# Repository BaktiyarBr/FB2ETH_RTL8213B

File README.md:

# FB2ETH for OpenIPC

A small fiber-to-Ethernet media converter board for [OpenIPC](https://openipc.org) cameras. It connects a camera's 10/100 Ethernet port to a single-fiber BiDi SFP optical module, so the camera can be linked over optical fiber instead of copper.

The board is designed in KiCad 10.

## How it works

| Block | Part | Role |
|-------|------|------|
| Ethernet / SerDes switch | **RTL8213B-CG** (U1) | Bridges the camera's copper Ethernet (MDI) to the SFP's high-speed serial lanes |
| Power | **MP9943GQ-Z** (U3) + 10 µH inductor (L2) | Buck converter that makes the +3V3 rail from the camera's VBUS |
| Clock | 25 MHz crystal (X2) | Reference clock for the RTL8213B |
| Status | 3 × 0402 LEDs (PWR1, P6S1, P6S2) | Power and port link/activity |
| Camera side | **J1** – JST SH 1.0 mm, 6-pin | Ethernet + power from the camera |
| Fiber side | **J2** – 9-pin SFP BiDi module socket | Optical transceiver |

### J1 – camera connector (JST SH, 6-pin)

| Pin | Signal |
|-----|--------|
| 1 | ETH_TX+ |
| 2 | ETH_TX− |
| 3 | ETH_RX+ |
| 4 | ETH_RX− |
| 5 | GND |
| 6 | VBUS (power in) |

### J2 – SFP BiDi module (9-pin)

| Pin | Signal |
|-----|--------|
| 1 | GND |
| 2 | RXP |
| 3 | RXN |
| 4 | SD (signal detect) |
| 5, 6 | +3V3 |
| 7 | SFP_TX_N |
| 8 | SFP_TX_P |
| 9 | GND |

## Repository layout

```
FB2ETH_3/FB2ETH_3/     Current revision (4-layer PCB) — start here
  FB2ETH_3.kicad_pro   KiCad project
  FB2ETH_3.kicad_sch   Schematic
  FB2ETH_3.kicad_pcb   PCB layout
  FB2ETH_3.kicad_dru   Custom design rules
  FB2ETH_3.csv         Full BOM with LCSC part numbers
  production/          Gerbers (zip), BOM, pick-and-place, IPC netlist for JLCPCB
FB2ETH_2/FB2ETH_2/     Previous revision
FB2ETH/                First revision
from_epro/             Original EasyEDA Pro design imported into KiCad (reference)
projectLibs.pretty/    Project footprints (SFP connectors, QFN-8 for MP9943)
```

The `*-backups/` folders are KiCad's automatic project backups.

## Manufacturing

The `production/` folder of each revision is generated with the KiCad [Fabrication Toolkit](https://github.com/bennymeg/Fabrication-Toolkit) plugin (settings in `fabrication-toolkit-options.json`) and is ready to upload to JLCPCB:

- `FB2ETH_3.zip` – Gerber and drill files
- `bom.csv` – bill of materials for assembly
- `positions.csv` – component placement (CPL)

To regenerate them, open `FB2ETH_3.kicad_pcb` in KiCad and run **Fabrication Toolkit** from the PCB editor's plugin menu.

## Opening the project

1. Install [KiCad](https://www.kicad.org/) 10 or newer.
2. Open `FB2ETH_3/FB2ETH_3/FB2ETH_3.kicad_pro`.
3. If footprints show as missing, add `projectLibs.pretty` to the project's footprint library table under the nickname `projectLibs`.

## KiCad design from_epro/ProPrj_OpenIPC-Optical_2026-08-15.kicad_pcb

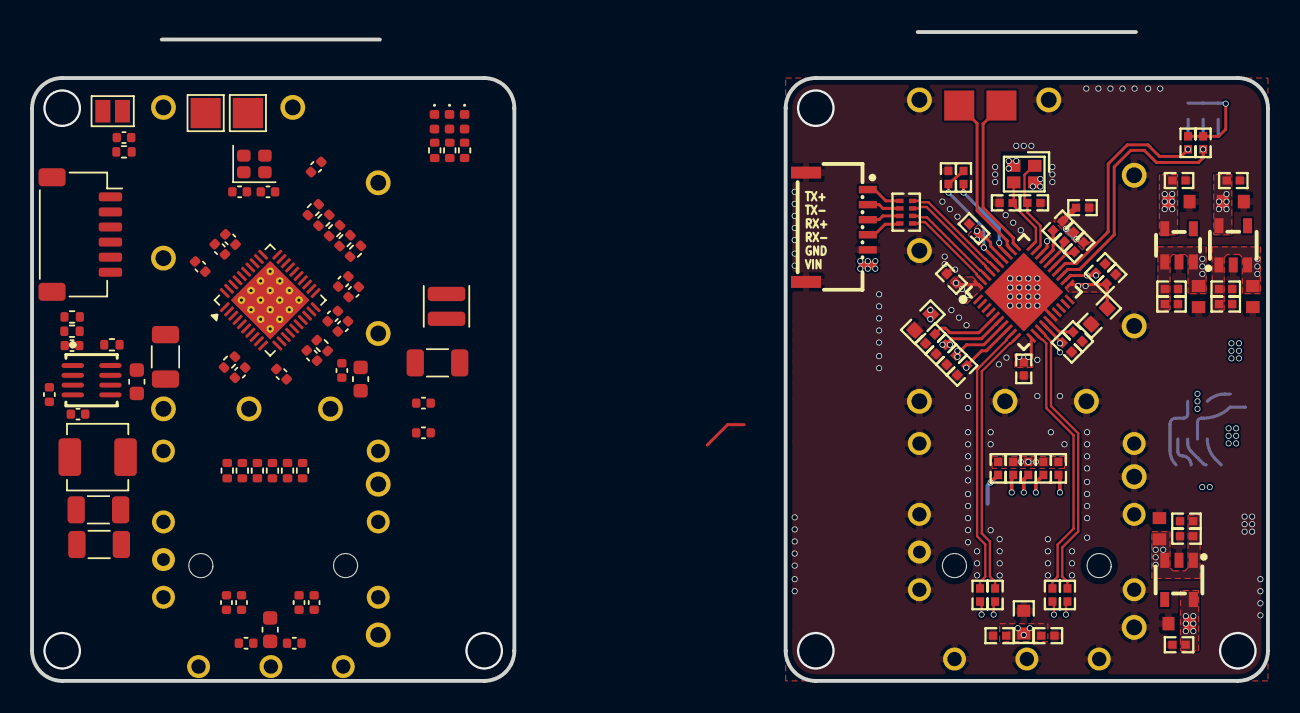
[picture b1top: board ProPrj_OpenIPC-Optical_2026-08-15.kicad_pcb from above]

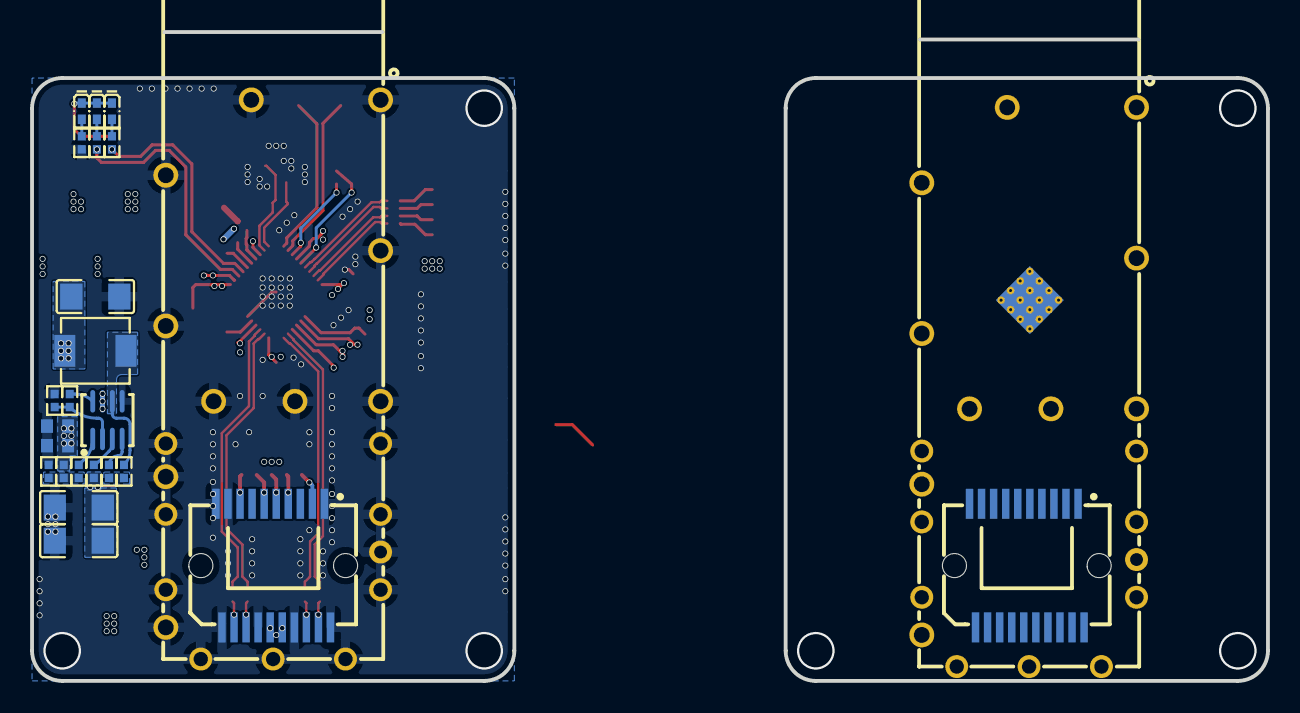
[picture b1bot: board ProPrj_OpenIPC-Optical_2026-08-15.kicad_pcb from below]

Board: 4 copper layers, 82.0 x 43.0 mm, 149 parts (25 on the bottom side), 92 nets.

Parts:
C1, C2#2: 18pF; C_0402_1005Metric
C1#2, C2, C3, C4, C5, C6, C7, C8, C10, C11, C12, C13, C14, C46, C68, C70, C71, C72, C73, C76, C81, C85, C88, C96, C97, C99, C100, C102: R0402
C9, C69, C75: R0603
C15, C16, C17, C18, C21, C22, C23, C26, C27, C28, C29, C30, C31, C32, C33, C35, C36, C38, C39, C40, C41, C42, C43, C44: 100n; C_0402_1005Metric
C15#2, C77, C80, C84, C94, C95, C98, C101: C0603
C18#2, C19#2, C93: C1206
C19, C20: 22u; C_1206_3216Metric
C20#2, C78: C0402
C24: 100n; C_0603_1608Metric
C25, C34: 10u; C_1206_3216Metric
C37, C45: 1u; C_0603_1608Metric
CN1: HC-SFP-20P; CONN-SMD_20P-P0.80_HCTL_HC-SFP-20P
CN1#2: CONN-SMD_20P-P0.80_HCTL_HC-SFP-20P
J1: Conn_01x06_MountingPin; JST_SH_SM06B-SRSS-TB_1x06-1MP_P1.00mm_Horizontal
JP1: SolderJumper_2_Open; SolderJumper-2_P1.3mm_Open_Pad1.0x1.5mm
L1: 2u2; L_Changjiang_FTC252012S
L1#2: IND-SMD_L4.4-W4.2
L2: 10uH; L_Changjiang_FXL0420
P6S0, P6S1#2: LED0402-RD
P6S1, P6S2: LED_0402_1005Metric
PWR: LED0402-RD
PWR1: LED_0402_1005Metric
R1, R2, R3, R4, R10, R11#2, R95#2: 4.7kΩ; R_0402_1005Metric
R1#2, R2#2, R3#2, R4#2, R5#2, R6#2, R9#2, R10#2, R11, R16, R17, R20, R82, R83, R86, R87#2, R90, R95, R96, R97, R98, R99#2: R0402
R5, R6, R99: 470Ω; R_0402_1005Metric
R7, R12: 100k; R_0402_1005Metric
R8: 43k; R_0402_1005Metric
R9: 2.49kΩ; R_0402_1005Metric
R13: 1k; R_0402_1005Metric
R82#2, R83#2, R86#2, R87, R90#2: 10kΩ; R_0402_1005Metric
RN1: RES-ARRAY-SMD_0402-8P-L2.0-W1.0-BL
SCK: Test-Point-0.5mm
SCK1: TestPoint_Pad_2.0x2.0mm
SDA: Test-Point-0.5mm
SDA1: TestPoint_Pad_2.0x2.0mm
TOMinBoard: CONN-SMD_6P-P1.00_HDGC1002WR-S-6P
U1: RTL8213B-CG; VQFN-40-1EP_5x5mm_P0.4mm_EP3.7x3.7mm_ThermalVias
U1#2: QFN-40_L5.0-W5.0-P0.40-BL-EP3.7
U2: QFN-8_L3.0-W3.0-P0.65-BL
U3: MP9943GQ-Z; QFN-8_L3.0-W3.0-P0.65-BL
U6: TH_HC-SFP-01L
U6#2: TH_HC-SFP-01L
U7, U8: SOT-23-5_L3.0-W1.7-P0.95-LS2.8-BR
U10: SOT-23-5_L2.9-W1.6-P0.95-LS2.8-BL
X2: 25MHz; Crystal_SMD_2016-4Pin_2.0x1.6mm
X2#2: CRYSTAL-SMD_4P-L2.0-W1.6-BL

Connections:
4V5: C15#2.2, C46.1, C77.2, C81.2, C85.2, C88.1, C93.1, C94.2, C95.2, C99.2, C100.1, C101.2, L1#2.2, R17.2, U7.1, U7.3, U8.1, U8.3, U10.1, U10.3
8213B_1V0: C3.2, C4.2, C5.2, C6.2, C7.2, C8.2, C75.2, C98.2, C102.1, U1#2.6, U1#2.8, U1#2.11, U1#2.22, U1#2.34, U1#2.40, U10.5
8213B_3V3: C9.2, C10.2, C11.2, C12.2, C13.2, C14.2, C80.2, C96.1, P6S0.1, P6S1#2.1, PWR.1, R1#2.2, R2#2.1, R3#2.2, R4#2.2, R10#2.2, R95.2, U1#2.7, U1#2.14, U1#2.21, U1#2.28, U1#2.35, U7.5
8213B_EN_SWR: R11.2, U1#2.15
8213B_SCK: SCK.1, U1#2.32
8213B_SDA: SDA.1, U1#2.31
$1N1852: C1#2.1, U1#2.29, X2#2.1
$1N1863: R10#2.1, U1#2.33
$1N1904: R9#2.2, U1#2.5
$1N1912: C2.2, U1#2.30, X2#2.3
$1N1945: P6S1#2.2, R5#2.2
$1N1946: P6S0.2, R6#2.2
$1N2817: CN1#2.5, R86.1
$1N2818: CN1#2.4, R83.1
$1N2820: CN1#2.6, R87#2.1
$1N2821: CN1#2.2, R82.1
$1N2827: CN1#2.8, R90.1
$1N6453: PWR.2, R99#2.2
$2N900: R97.2, U2.8
$2N902: C20#2.2, R98.2
$2N903: C78.2, R97.1, U2.2
$2N910: R16.2, R17.1, R20.2
$2N915: C20#2.1, U2.4
$2N918: R96.2, U2.3
+1V1: C28.1, C29.1, C30.1, C31.1, C32.1, C33.1, C34.1, L1.1, U1.6 (AVDDL), U1.8 (DVDDL), U1.11 (SVDDL), U1.22 (DVDDL), U1.34 (PLLVDDL), U1.40 (AVDDL)
+3V3: C16.1, C18.1, C19.1, C20.1, C21.1, C22.1, C26.1, C27.1, C35.1, C36.1, C37.1, C42.1, C43.1, C44.1, C45.1, CN1.15, CN1.16, L2.2, P6S1.1 (A), P6S2.1 (A), PWR1.1 (A), R1.2, R2.1, R3.2, R4.2, R7.1, R10.2, R11#2.1, R82#2.2, R83#2.2, R86#2.2, R87.2, R90#2.2, R95#2.2, U1.7 (AVDDH), U1.14 (AVDDH), U1.19 (HV_SWR), U1.20 (HV_SWR), U1.21 (DVDDIO), U1.28 (AVDDH), U1.35 (AVDDH)
/8213B_SCK: SCK1.1 (1_1), U1.32 (SCK)
/8213B_SDA: SDA1.1 (1_1), U1.31 (SDA)
/ETH_RX+: J1.3, U1.38 (P3MDIBP)
/ETH_RX-: J1.4, U1.39 (P3MDIBN)
/ETH_TX+: J1.1, U1.36 (P3MDIAP)
/ETH_TX-: J1.2, U1.37 (P3MDIAN)
/HSIN: C41.2, U1.13 (HSIN)
/HSIP: C40.2, U1.12 (HSIP)
/HSON: C38.2, U1.9 (HSON)
/HSOP: C39.2, U1.10 (HSOP)
/P3LED0: R1.1, U1.27 (GPO52/P3LED0/SMI_SEL)
/P3LED1: R95#2.1, U1.26 (GPIO51/P3LED1)
/P3LED2: R2.2, U1.25 (GPO50/P3LED2/EN_PHY)
/P6LED0: R3.1, R6.1, U1.24 (GPIO48/P6LED0/MID29)
/P6LED1: R4.1, R5.1, U1.23 (GPO45/P6LED1/DISAUTOLOAD)
/SFP_RX_N: C41.1, CN1.12
/SFP_RX_P: C40.1, CN1.13
/SFP_TX_N: C38.1, CN1.19
/SFP_TX_P: C39.1, CN1.18
ETH_RX+: RN1.2, TOMinBoard.3
ETH_RX-: RN1.1, TOMinBoard.4
ETH_TX+: RN1.4, TOMinBoard.1
ETH_TX-: RN1.3, TOMinBoard.2
FB_5V: R16.1, U2.1
GND: C1.2, C1#2.2, C2.1, C2#2.1, C3.1, C4.1, C5.1, C6.1, C7.1, C8.1, C9.1, C10.1, C11.1, C12.1, C13.1, C14.1, C15.2, C15#2.1, C16.2, C18#2.1, C19.2, C19#2.1, C20.2, C21.2, C22.2, C23.2, C24.2, C25.2, C26.2, C27.2, C28.2, C29.2, C30.2, C31.2, C32.2, C33.2, C34.2, C35.2, C36.2, C37.2, C42.2, C43.2, C44.2, C45.2, C46.2, C68.1, C69.1, C75.1, C76.1, C77.1, C78.1, C80.1, C81.1, C84.1, C85.1, C88.2, C93.2, C94.1, C95.1, C96.2, C97.2, C98.1, C99.1, C100.2, C101.1, C102.2, CN1.1, CN1.9, CN1.10, CN1.11, CN1.14, CN1.17, CN1.20, CN1#2.1, CN1#2.9, CN1#2.10, CN1#2.11, CN1#2.14, CN1#2.17, CN1#2.20, J1.5, J1.MP (MountPin), JP1.1 (A), R8.2, R9.1, R9#2.1, R11.1, R13.2, R20.1, R99.1, R99#2.1, TOMinBoard.5, TOMinBoard.7, TOMinBoard.8, U1.16 (GND_SWR), U1.41 (EP), U1#2.16, U1#2.41, U2.5, U3.5 (GND), U6.1, U6.2, U6.3, U6.4, U6.5, U6.6, U6.7, U6.8, U6.9, U6.10, U6.11, U6.12, U6.13, U6.14, U6.15, U6.16, U6.17, U6.18, U6.19, U6.20, U6#2.1, U6#2.2, U6#2.3, U6#2.4, U6#2.5, U6#2.6, U6#2.7, U6#2.8, U6#2.9, U6#2.10, U6#2.11, U6#2.12, U6#2.13, U6#2.14, U6#2.15, U6#2.16, U6#2.17, U6#2.18, U6#2.19, U6#2.20, U7.2, U8.2, U10.2, X2.2 (GND), X2.4 (GND), X2#2.2, X2#2.4
HSIN: C73.2, U1#2.13
HSIP: C72.2, U1#2.12
HSON: C70.2, U1#2.9
HSOP: C71.2, U1#2.10
LC_5V: L1#2.1, R98.1, U2.6
unnamed: CN1.2, R82#2.1
unnamed: CN1.3, R13.1
unnamed: CN1.4, R83#2.1
unnamed: CN1.5, R86#2.1
unnamed: CN1.6, R87.1
unnamed: CN1.8, R90#2.1
unnamed: C15.1, JP1.2 (B), R10.1, U1.33 (nRESET)
unnamed: L1.2, U1.17 (LX), U1.18 (LX)
unnamed: P6S1.2 (K), R5.2
unnamed: P6S2.2 (K), R6.2
unnamed: PWR1.2 (K), R99.2
unnamed: R11#2.2, U1.15 (EN_SWR)
unnamed: R9.2, U1.5 (MDIREF)
unnamed: C2#2.2, U1.30 (XTALI), X2.3
unnamed: C1.1, U1.29 (XTALO), X2.1
unnamed: C17.1, U3.4 (BST)
unnamed: C18.2, R7.2, R8.1, U3.1 (FB)
unnamed: R12.1, U3.8 (PG)
unnamed: C17.2, L2.1, U3.6 (SW)
unnamed: C23.1, R12.2, U3.2 (VCC)
P0MDIAN: RN1.6, U1#2.37
P0MDIAP: RN1.5, U1#2.36
P0MDIBN: RN1.8, U1#2.39
P0MDIBP: RN1.7, U1#2.38
P3LED0: R1#2.1, U1#2.27
P3LED1: R95.1, U1#2.26
P3LED2: R2#2.2, U1#2.25
P6LED0: R3#2.1, R6#2.1, U1#2.24
P6LED1: R4#2.1, R5#2.1, U1#2.23
SFP_3V3: C68.2, C69.2, C76.2, C84.2, C97.1, CN1#2.15, CN1#2.16, R82.2, R83.2, R86.2, R87#2.2, R90.2, U8.5
SFP_RX_N: C73.1, CN1#2.12
SFP_RX_P: C72.1, CN1#2.13
SFP_TX_N: C70.1, CN1#2.19
SFP_TX_P: C71.1, CN1#2.18
VBAT: C18#2.2, C19#2.2, R96.1, TOMinBoard.6, U2.7
VBUS: C24.1, C25.1, J1.6, U3.3 (EN/SYNC), U3.7 (IN)

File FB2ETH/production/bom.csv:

Designator,Footprint,Quantity,Value,LCSC Part #
"C19, C20",1206,2,22u,
"C25, C34",1206,2,10u,
CN1,CONN-SMD_20P-P0.80_HCTL_HC-SFP-20P,1,HC-SFP-20P,
J1,JST_SH_SM06B-SRSS-TB_1x06-1MP_P1.00mm_Horizontal,1,Conn_01x06_MountingPin,
L1,L_Changjiang_FTC252012S,1,2u2,
L2,L_Changjiang_FXL0420,1,10uH,
"P6S1, P6S2, PWR1",0402,3,~,
R8,0402,1,43k,
U1,VQFN-40-1EP_5x5mm_P0.4mm_EP3.7x3.7mm_ThermalVias,1,RTL8213B-CG,
U3,QFN-8_L3.0-W3.0-P0.65-BL,1,MP9943GQ-Z,
U6,TH_HC-SFP-01L,1,~,
X2,Crystal_SMD_2016-4Pin_2.0x1.6mm,1,25MHz,
